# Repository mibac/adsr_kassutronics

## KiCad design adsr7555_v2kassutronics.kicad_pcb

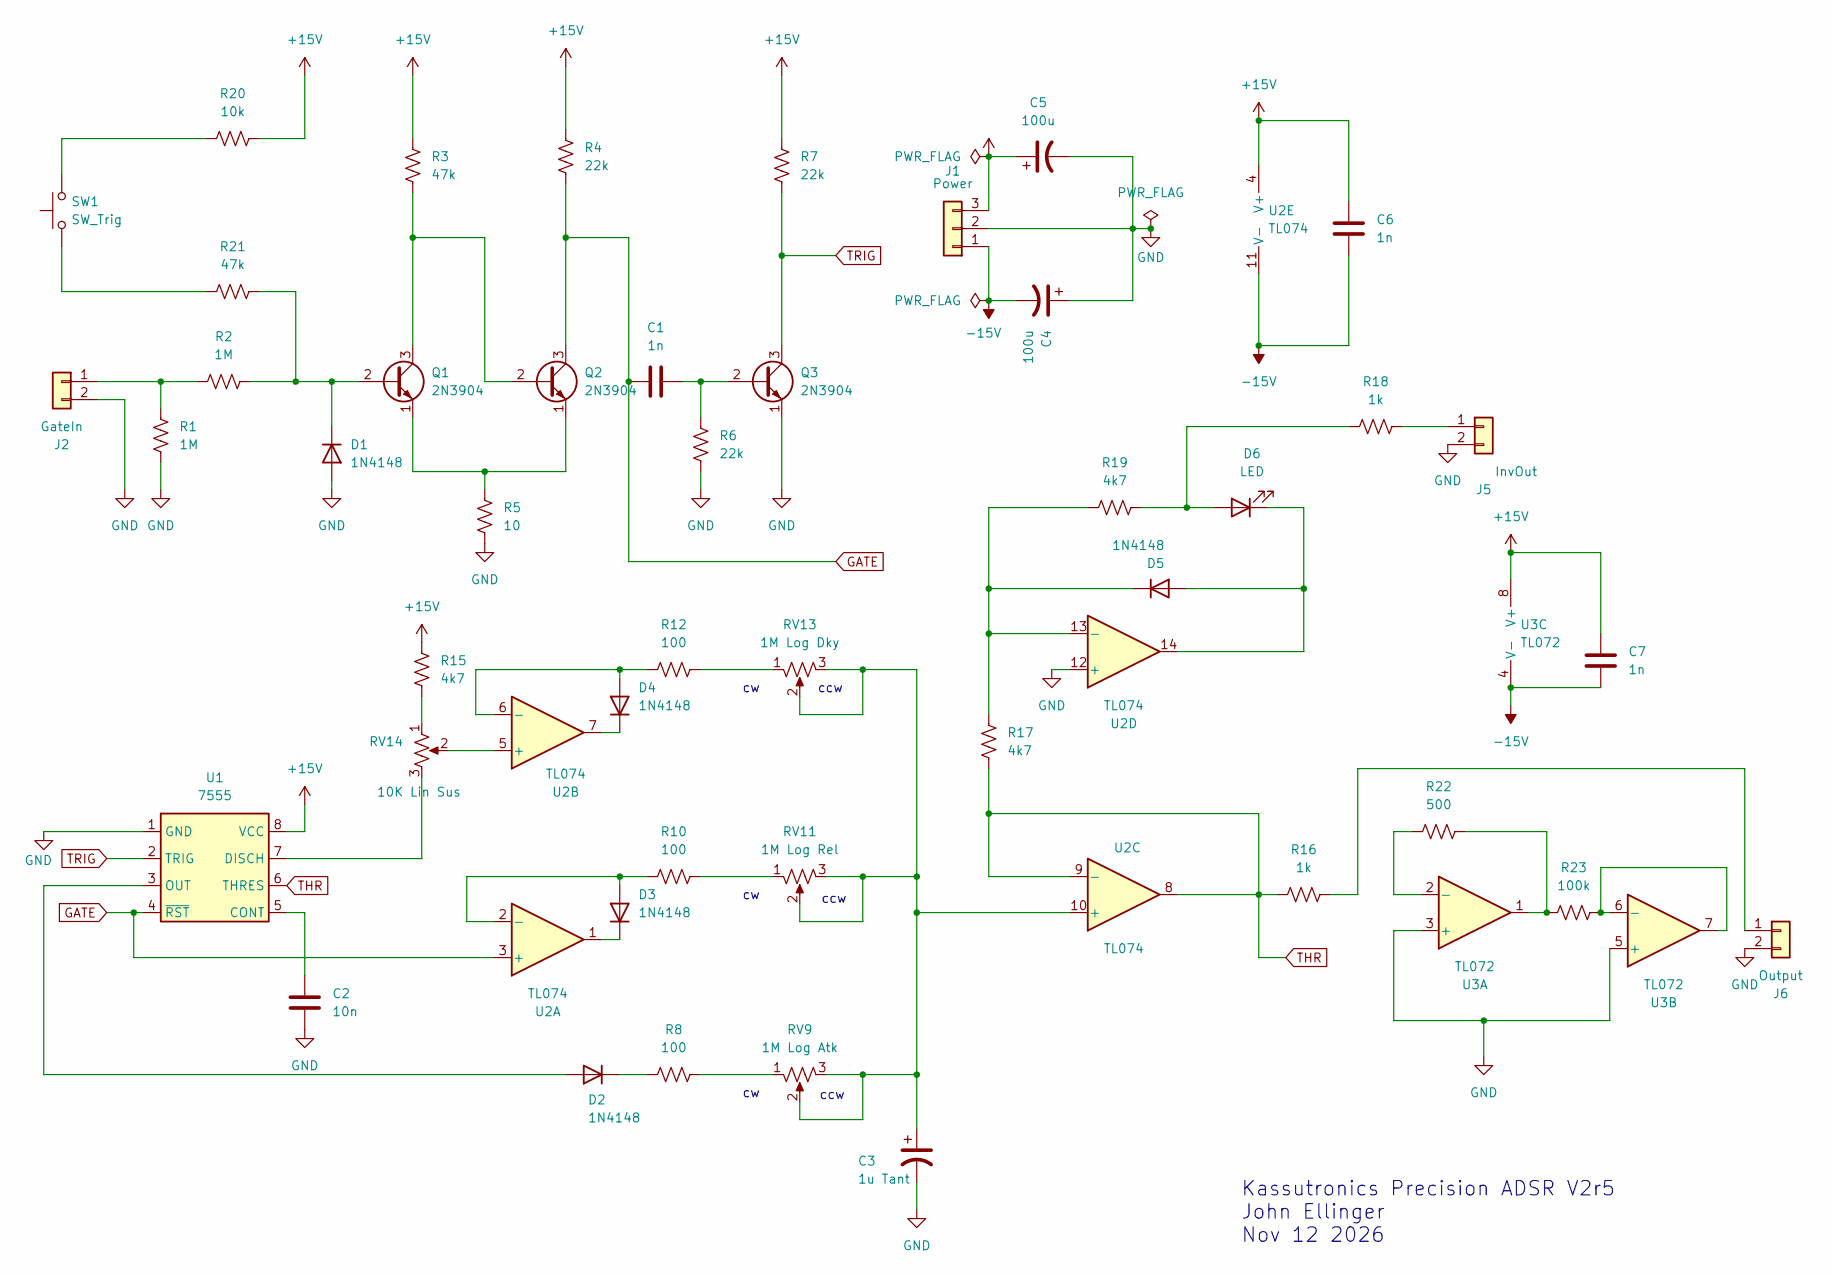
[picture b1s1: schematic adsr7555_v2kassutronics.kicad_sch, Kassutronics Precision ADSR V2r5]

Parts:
C1, C6, C7: 1n; C_Disc_D4.7mm_W2.5mm_P5.00mm
C2: 10n; C_Disc_D4.7mm_W2.5mm_P5.00mm
C3: 1u Tant; CP_Radial_D5.0mm_P2.50mm
C4, C5: 100u; CP_Radial_D5.0mm_P2.50mm
D1, D2, D3, D5: 1N4148; D_DO-35_SOD27_P7.62mm_Horizontal
D4: 1N4148; D_DO-34_SOD68_P2.54mm_Vertical_AnodeUp
D6: LED; Molex_KK-254_AE-6410-02A_1x02_P2.54mm_Vertical
J1: Power; Molex_KK-254_AE-6410-03A_1x03_P2.54mm_Vertical
J2: GateIn; Molex_KK-254_AE-6410-02A_1x02_P2.54mm_Vertical
J5: InvOut; Molex_KK-254_AE-6410-02A_1x02_P2.54mm_Vertical
J6: Output; Molex_KK-254_AE-6410-02A_1x02_P2.54mm_Vertical
Q1, Q2, Q3: 2N3904; TO-92L_Inline_Wide
R1, R2: 1M; R_Axial_DIN0204_L3.6mm_D1.6mm_P7.62mm_Horizontal
R3, R21: 47k; R_Axial_DIN0204_L3.6mm_D1.6mm_P7.62mm_Horizontal
R4, R6, R7: 22k; R_Axial_DIN0204_L3.6mm_D1.6mm_P7.62mm_Horizontal
R5: 10; R_Axial_DIN0204_L3.6mm_D1.6mm_P7.62mm_Horizontal
R8, R10, R12: 100; R_Axial_DIN0204_L3.6mm_D1.6mm_P7.62mm_Horizontal
R15, R17, R19: 4k7; R_Axial_DIN0204_L3.6mm_D1.6mm_P7.62mm_Horizontal
R16, R18: 1k; R_Axial_DIN0204_L3.6mm_D1.6mm_P7.62mm_Horizontal
R20: 10k; R_Axial_DIN0204_L3.6mm_D1.6mm_P7.62mm_Horizontal
R22: 500; R_Axial_DIN0204_L3.6mm_D1.6mm_P7.62mm_Horizontal
R23: 100k; R_Axial_DIN0204_L3.6mm_D1.6mm_P7.62mm_Horizontal
RV9: 1M Log Atk; Molex_KK-254_AE-6410-03A_1x03_P2.54mm_Vertical
RV11: 1M Log Rel; Molex_KK-254_AE-6410-03A_1x03_P2.54mm_Vertical
RV13: 1M Log Dky; Molex_KK-254_AE-6410-03A_1x03_P2.54mm_Vertical
RV14: 10K Lin Sus; Molex_KK-254_AE-6410-03A_1x03_P2.54mm_Vertical
SW1: SW_Trig; Molex_KK-254_AE-6410-02A_1x02_P2.54mm_Vertical
U1: 7555; DIP-8_W7.62mm
U2: TL074; DIP-14_W7.62mm_Socket
U3: TL072; DIP-8_W7.62mm

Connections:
+15V: C5.1, C6.2, C7.2, J1.3, R3.2, R4.2, R7.2, R15.2, R20.2, U1.8 (VCC), U2.4 (V+), U3.8 (V+)
-15V: C4.2, C6.1, C7.1, J1.1, U2.11 (V-), U3.4 (V-)
GATE: C1.1, Q2.3 (C), R4.1, U1.4 (~RST), U2.3 (+)
GND: C2.2, C3.2, C4.1, C5.2, D1.2 (A), J1.2, J2.2, J5.2, J6.2, Q3.1 (E), R1.1, R5.1, R6.1, U1.1 (GND), U2.12 (+), U3.3 (+), U3.5 (+)
unnamed: D1.1 (K), Q1.2 (B), R2.2, R21.2
unnamed: D2.2 (A), U1.3 (OUT)
unnamed: D2.1 (K), R8.1
unnamed: D3.2 (A), R10.1, U2.2 (-)
unnamed: D3.1 (K), U2.1
unnamed: D4.2 (A), R12.1, U2.6 (-)
unnamed: D4.1 (K), U2.7
unnamed: D5.2 (A), D6.1 (K), U2.14
unnamed: D5.1 (K), R17.2, R19.2, U2.13 (-)
unnamed: D6.2 (A), R18.2, R19.1
unnamed: J2.1, R1.2, R2.1
unnamed: J5.1, R18.1
unnamed: J6.1, R16.1
unnamed: Q1.3 (C), Q2.2 (B), R3.1
unnamed: Q1.1 (E), Q2.1 (E), R5.2
unnamed: C1.2, Q3.2 (B), R6.2
unnamed: R8.2, RV9.1
unnamed: R10.2, RV11.1
unnamed: R12.2, RV13.1
unnamed: R15.1, RV14.1
unnamed: R20.1, SW1.2
unnamed: R21.1, SW1.1
unnamed: R22.1, R23.2, U3.1
unnamed: C2.1, U1.5 (CONT)
unnamed: RV14.3, U1.7 (DISCH)
unnamed: RV14.2, U2.5 (+)
unnamed: C3.1, RV9.2, RV9.3, RV11.2, RV11.3, RV13.2, RV13.3, U2.10 (+)
unnamed: R22.2, U3.2 (-)
unnamed: R23.1, U3.6 (-), U3.7
THR: R16.2, R17.1, U1.6 (THRES), U2.8, U2.9 (-)
TRIG: Q3.3 (C), R7.1, U1.2 (TRIG)

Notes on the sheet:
ccw
Kassutronics Precision ADSR V2r5 John Ellinger Nov 12 2026

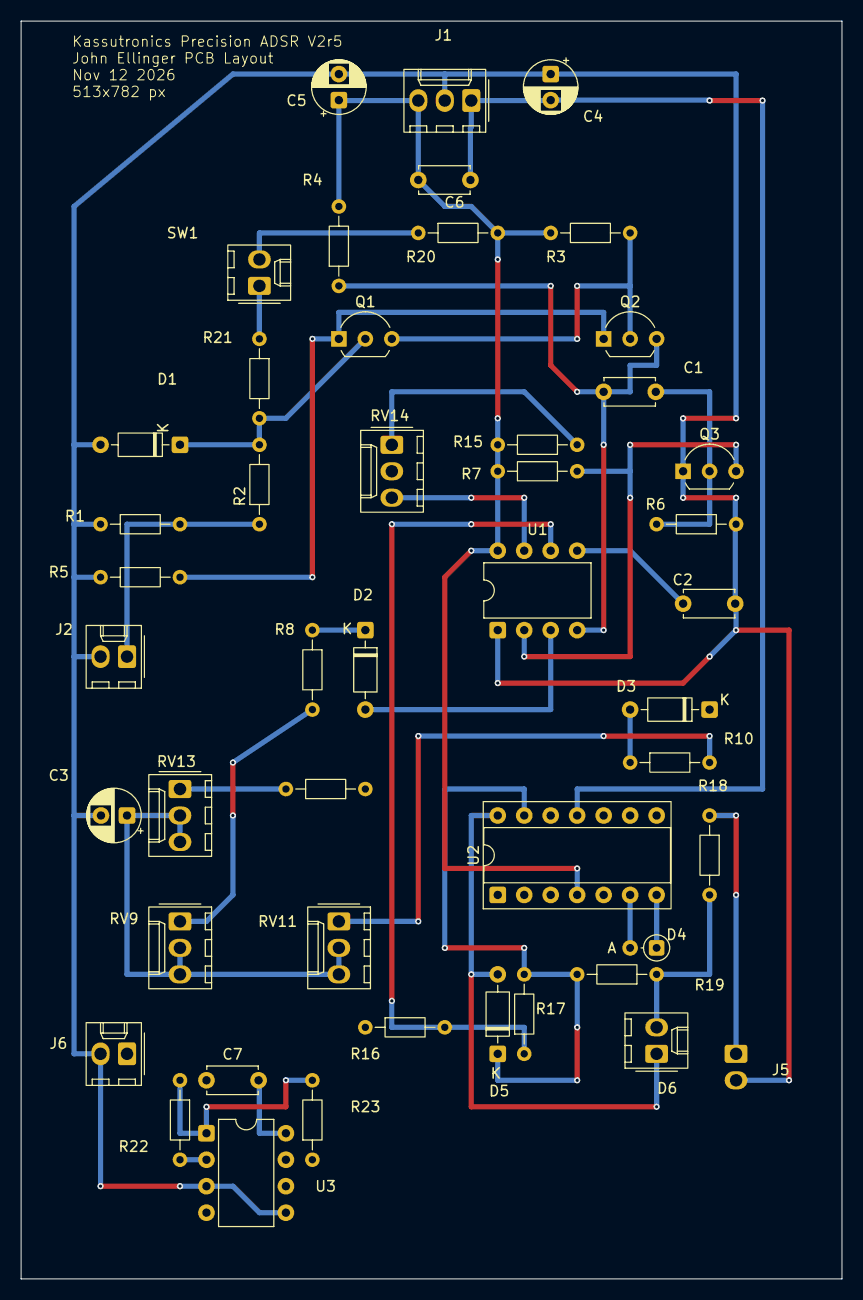
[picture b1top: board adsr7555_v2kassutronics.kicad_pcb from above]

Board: 8 copper layers, 78.7 x 120.7 mm, 47 parts (1 on the bottom side), 35 nets.

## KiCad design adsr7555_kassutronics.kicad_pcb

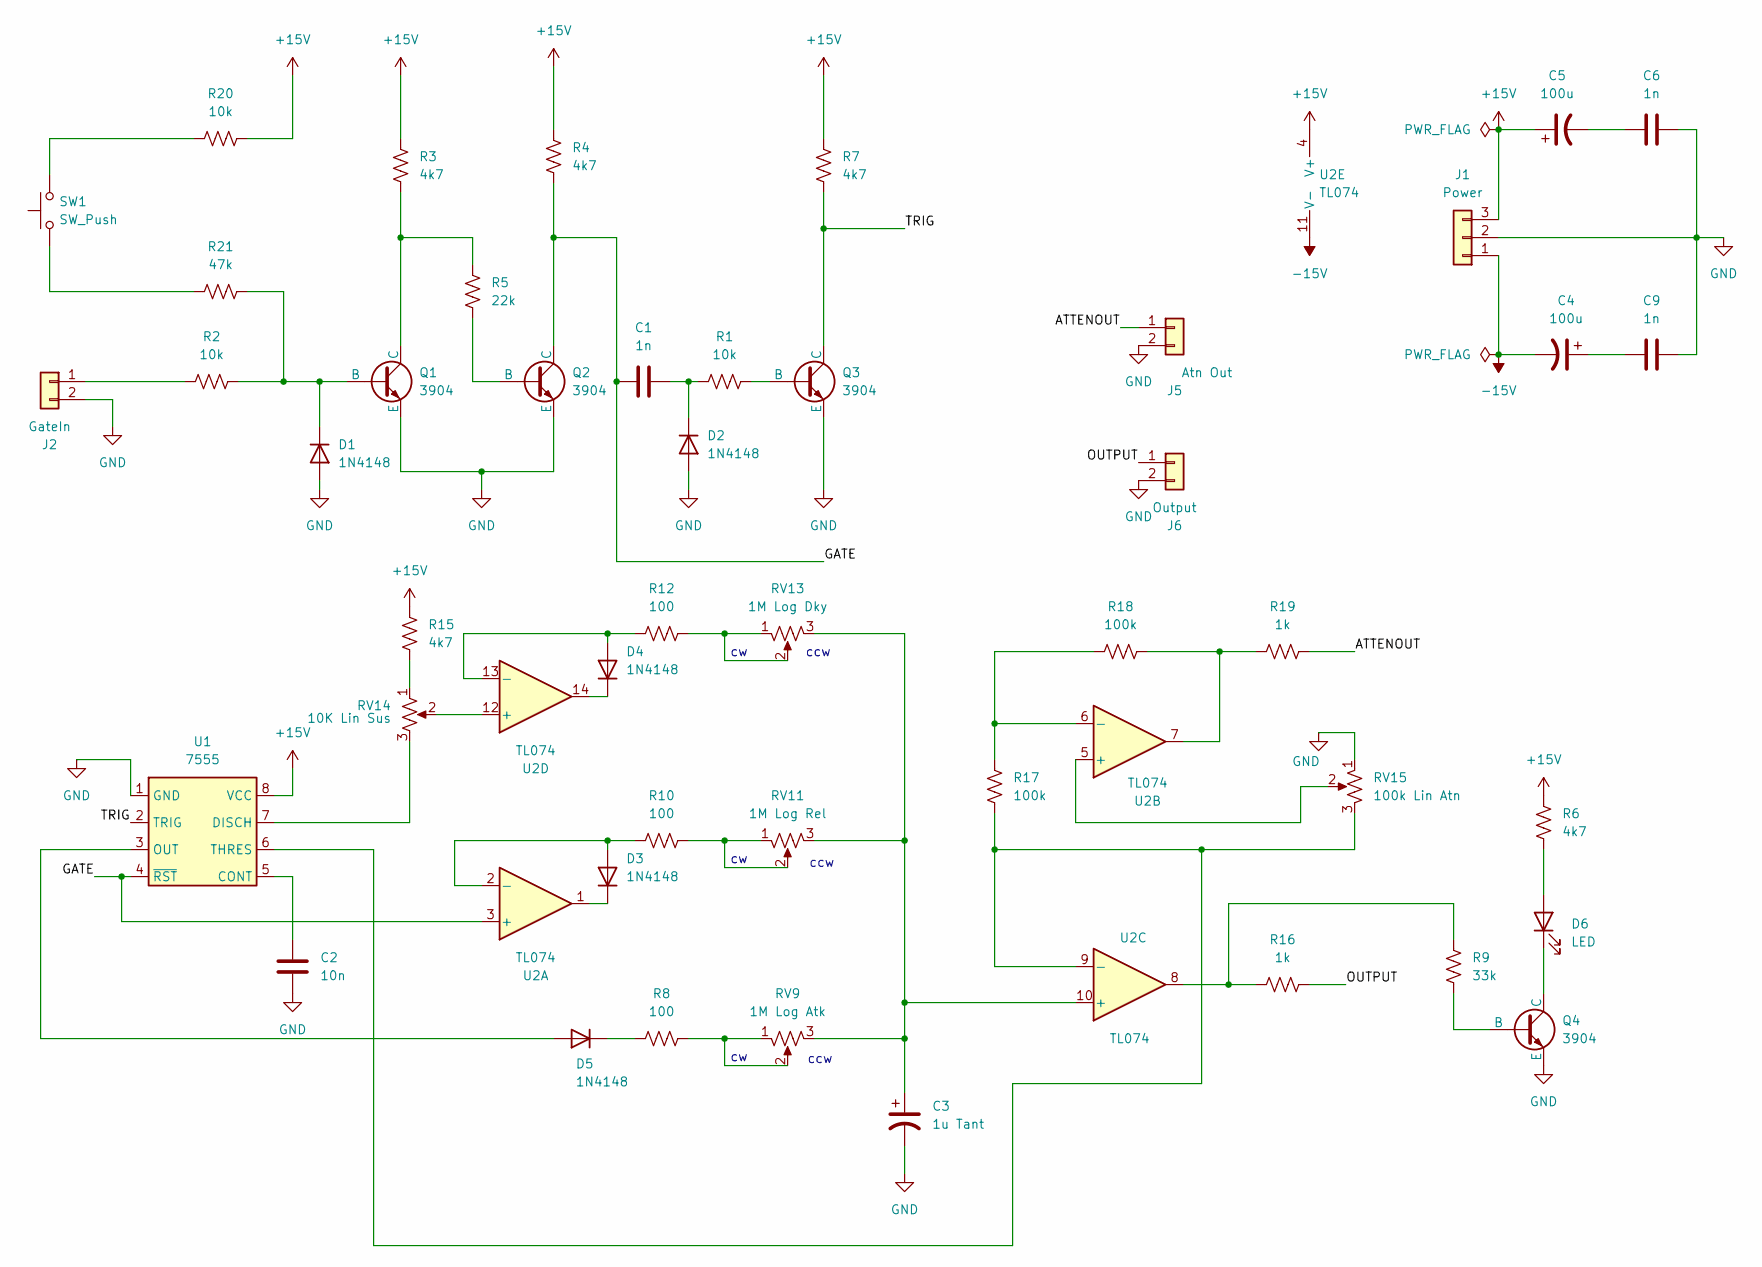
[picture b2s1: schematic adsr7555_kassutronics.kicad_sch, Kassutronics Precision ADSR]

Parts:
C1, C6, C9: 1n; C_Disc_D4.7mm_W2.5mm_P5.00mm
C2: 10n; C_Disc_D4.7mm_W2.5mm_P5.00mm
C3: 1u Tant; CP_Radial_D5.0mm_P2.50mm
C4, C5: 100u; CP_Radial_D4.0mm_P2.00mm
D1, D2, D3, D4, D5: 1N4148; D_DO-35_SOD27_P7.62mm_Horizontal
D6: LED; Molex_KK-254_AE-6410-02A_1x02_P2.54mm_Vertical
J1: Power; Molex_KK-254_AE-6410-03A_1x03_P2.54mm_Vertical
J2: GateIn; Molex_KK-254_AE-6410-02A_1x02_P2.54mm_Vertical
J5: Atn Out; Molex_KK-254_AE-6410-02A_1x02_P2.54mm_Vertical
J6: Output; Molex_KK-254_AE-6410-02A_1x02_P2.54mm_Vertical
Q1, Q2, Q3, Q4: 3904; TO-92L_Inline_Wide
R1, R2, R20: 10k; R_Axial_DIN0204_L3.6mm_D1.6mm_P7.62mm_Horizontal
R3, R4, R6, R7, R15: 4k7; R_Axial_DIN0204_L3.6mm_D1.6mm_P7.62mm_Horizontal
R5: 22k; R_Axial_DIN0204_L3.6mm_D1.6mm_P7.62mm_Horizontal
R8, R10, R12: 100; R_Axial_DIN0204_L3.6mm_D1.6mm_P7.62mm_Horizontal
R9: 33k; R_Axial_DIN0204_L3.6mm_D1.6mm_P7.62mm_Horizontal
R16, R19: 1k; R_Axial_DIN0204_L3.6mm_D1.6mm_P7.62mm_Horizontal
R17, R18: 100k; R_Axial_DIN0204_L3.6mm_D1.6mm_P7.62mm_Horizontal
R21: 47k; R_Axial_DIN0204_L3.6mm_D1.6mm_P7.62mm_Horizontal
RV9: 1M Log Atk; Molex_KK-254_AE-6410-03A_1x03_P2.54mm_Vertical
RV11: 1M Log Rel; Molex_KK-254_AE-6410-03A_1x03_P2.54mm_Vertical
RV13: 1M Log Dky; Molex_KK-254_AE-6410-03A_1x03_P2.54mm_Vertical
RV14: 10K Lin Sus; Molex_KK-254_AE-6410-03A_1x03_P2.54mm_Vertical
RV15: 100k Lin Atn; Potentiometer_Bourns_3296W_Vertical
SW1: SW_Push; Molex_KK-254_AE-6410-02A_1x02_P2.54mm_Vertical
U1: 7555; DIP-8_W7.62mm
U2: TL074; DIP-14_W7.62mm_Socket

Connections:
+15V: C5.1, J1.3, R3.2, R4.2, R6.2, R7.2, R15.2, R20.2, U1.8 (VCC), U2.4 (V+)
-15V: C4.2, J1.1, U2.11 (V-)
/ATTENOUT: J5.1, R19.1
/GATE: C1.1, Q2.1 (C), R4.1, U1.4 (~RST), U2.3 (+)
/OUTPUT: J6.1, R16.1
/TRIG: Q3.1 (C), R7.1, U1.2 (TRIG)
GND: C2.2, C3.2, C6.2, C9.2, D1.2 (A), D2.2 (A), J1.2, J2.2, J5.2, J6.2, Q1.3 (E), Q2.3 (E), Q3.3 (E), Q4.3 (E), RV15.1, U1.1 (GND)
unnamed: C4.1, C9.1
unnamed: C5.2, C6.1
unnamed: D1.1 (K), Q1.2 (B), R2.2, R21.2
unnamed: C1.2, D2.1 (K), R1.1
unnamed: D3.2 (A), R10.1, U2.2 (-)
unnamed: D3.1 (K), U2.1
unnamed: D4.2 (A), R12.1, U2.13 (-)
unnamed: D4.1 (K), U2.14
unnamed: D5.2 (A), U1.3 (OUT)
unnamed: D5.1 (K), R8.1
unnamed: D6.2 (A), R6.1
unnamed: D6.1 (K), Q4.1 (C)
unnamed: J2.1, R2.1
unnamed: Q1.1 (C), R3.1, R5.2
unnamed: Q2.2 (B), R5.1
unnamed: Q3.2 (B), R1.2
unnamed: Q4.2 (B), R9.1
unnamed: R8.2, RV9.1, RV9.2
unnamed: R10.2, RV11.1, RV11.2
unnamed: R12.2, RV13.1, RV13.2
unnamed: R15.1, RV14.1
unnamed: R9.2, R16.2, U2.8
unnamed: R18.1, R19.2, U2.7
unnamed: R20.1, SW1.2
unnamed: R21.1, SW1.1
unnamed: C2.1, U1.5 (CONT)
unnamed: RV14.3, U1.7 (DISCH)
unnamed: R17.1, RV15.3, U1.6 (THRES), U2.9 (-)
unnamed: RV15.2, U2.5 (+)
unnamed: R17.2, R18.2, U2.6 (-)
unnamed: C3.1, RV9.3, RV11.3, RV13.3, U2.10 (+)
unnamed: RV14.2, U2.12 (+)

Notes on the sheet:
ccw

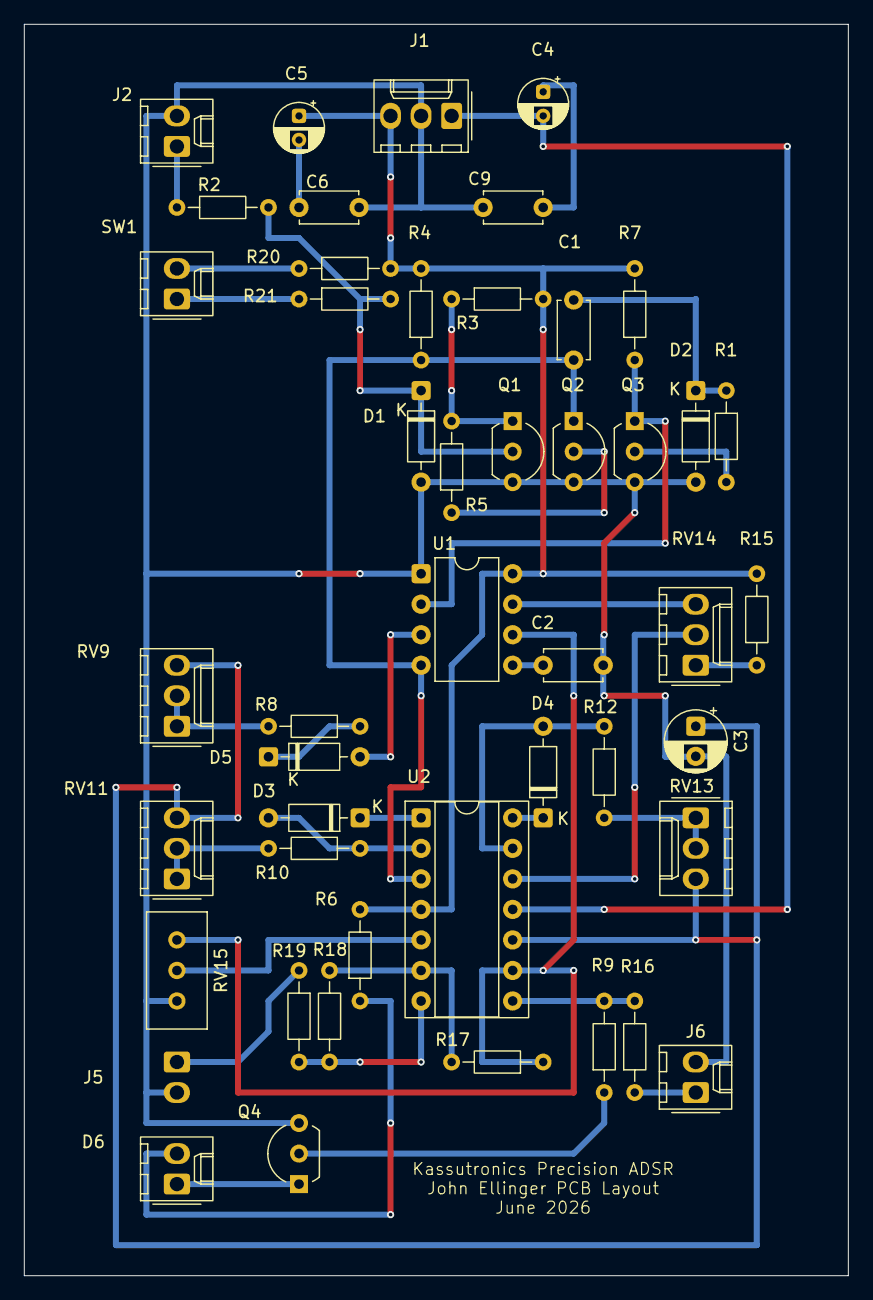
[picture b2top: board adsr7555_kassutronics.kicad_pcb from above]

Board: 2 copper layers, 68.6 x 104.1 mm, 47 parts (1 on the bottom side), 39 nets.

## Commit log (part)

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2026-06-10 added .gitignore
2026-06-10 SCH v1 needs QC against web schematic
2026-06-18 PCB layout in progress
2026-06-19 PCB Wiring complete. Need to fix silkscreen overlaps
2026-06-20 QA PCB passes
2026-06-20 removed TRIG and GATE panel connectors
2026-06-20 added pdf files for SCH and PCB from mac
2026-06-21 minor via moves
2026-06-21 created ibom and SCH.svg
2026-06-23 Wiring PCB top down. Next is U1
2026-06-23 PCB wiring need to finish U1 pins 5-8
2026-06-23 PCB more wiring. More to go
2026-06-24 mod .png/svg
2026-06-25 update PCB wiring worked on lower right
2026-06-25 wiring PCB lower right
2026-06-27 SVG QA1 wiring complete. TODO: QA2
2026-06-27 re-commit on save and exit
2026-06-28 QA2 completed
